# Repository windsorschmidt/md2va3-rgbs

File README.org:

* About

RGBS video and audio output board for Sega Genesis 2 VA3.

Based on the "Triple Bypass" (3BP for short) circuit originally from
René Richard.  Unlike the TBP which can be configured to work with
several types of Genesis consoles, this board is designed specifically
for the Genesis 2 VA3.

* Features

- Active buffer/amplifiers for audio and video
- Mounts inside console beside main PCB using existing mounting points
- RGBS output on DE-15 (VGA style) connector
- Audio output on 3.5mm phono jack

[[md2va3-rgbs.png?raw=true]]

* Status

Revision 2 PCB tested working.

* References

- https://github.com/db-electronics/triple-bypass-kicad
- https://github.com/tianfeng33/triple-bypass-Version-2

* License

Circuit schematic and PCB layout are licensed under CERN-OHL-S v2.

See [[LICENSE.txt]].

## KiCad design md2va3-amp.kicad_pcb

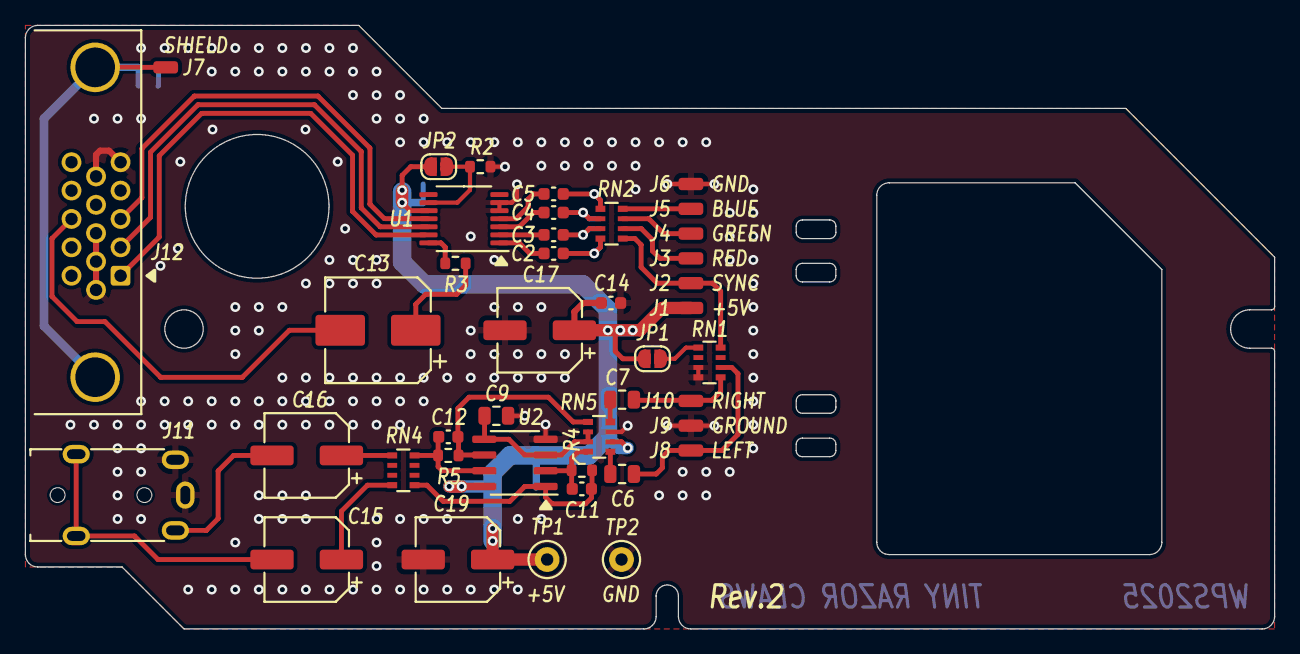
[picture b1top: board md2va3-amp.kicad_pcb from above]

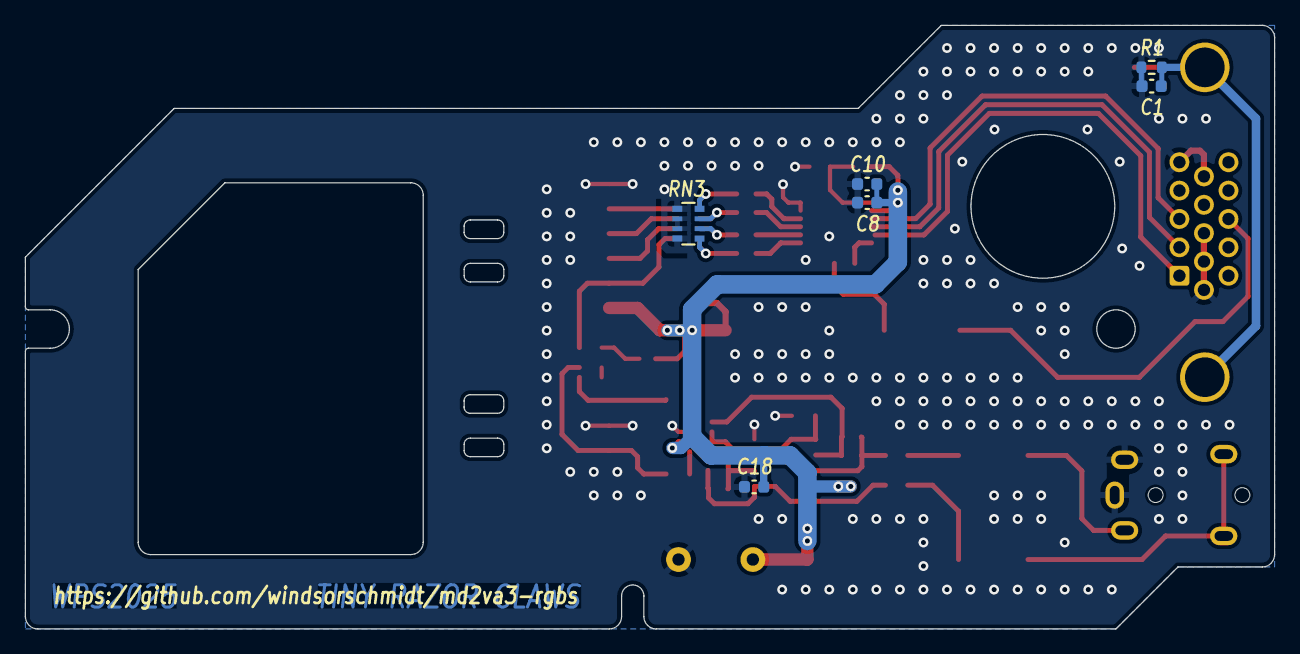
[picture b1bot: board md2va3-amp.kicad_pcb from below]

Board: 2 copper layers, 100.8 x 48.7 mm, 49 parts (6 on the bottom side), 36 nets.

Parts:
C1, C11, C12: 33p; C_0603_1608Metric
C2, C3, C4, C5, C14, C18: 100n; C_0603_1608Metric
C6, C7, C9: 10u; C_0805_2012Metric
C8: 10n; C_0603_1608Metric
C10: 1u; C_0603_1608Metric
C13: 220u; CP_Elec_8x6.2
C15, C16, C17, C19: 47u; CP_Elec_6.3x5.9
J1: +5V; SolderWirePad_1x01_SMD_1x2mm
J2: SYNC_TTL; SolderWirePad_1x01_SMD_1x2mm
J3: R; SolderWirePad_1x01_SMD_1x2mm
J4: G; SolderWirePad_1x01_SMD_1x2mm
J5: B; SolderWirePad_1x01_SMD_1x2mm
J6, J9: GND; SolderWirePad_1x01_SMD_1x2mm
J7: SHIELD; SolderWirePad_1x01_SMD_1x2mm
J8: LEFT; SolderWirePad_1x01_SMD_1x2mm
J10: RIGHT; SolderWirePad_1x01_SMD_1x2mm
J11: 54-00174; Jack_3.5mm_Tensility_54-00174
J12: HD15-SN-25; DSUB-15-HD_Female_Horizontal_P2.29x1.98mm_EdgePinOffset3.03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
JP1: SYNC_PU; SolderJumper-2_P1.3mm_Open_RoundedPad1.0x1.5mm
JP2: LPF; SolderJumper-2_P1.3mm_Open_RoundedPad1.0x1.5mm
MNT1, MNT2: MOUNT_ZIP_TIE; MountingHole_Zip_Tie
R1: 1M; R_0603_1608Metric
R2: 4.7k; R_0603_1608Metric
R3: 75; R_0603_1608Metric
R4, R5: 300k; R_0603_1608Metric
RN1: 2.2k; R_Array_Convex_4x0603
RN2: 5.62k; R_Array_Convex_4x0603
RN3: 1k; R_Array_Convex_4x0603
RN4: 330; R_Array_Convex_4x0603
RN5: 10k; R_Array_Convex_4x0603
TP1: +5V; TestPoint_Loop_D2.50mm_Drill1.0mm
TP2: GND; TestPoint_Loop_D2.50mm_Drill1.0mm
U1: THS7374; TSSOP-14_4.4x5mm_P0.65mm
U2: TLV9162IDR; SOIC-8_3.9x4.9mm_P1.27mm

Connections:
+5V: C8.1, C10.2, C14.1, C17.1, C18.1, C19.1, J1.1, JP1.1 (A), JP2.1 (A), RN5.6 (R3.2), TP1.1, U1.10 (V_{S+}), U2.8 (V+)
/B: J5.1, RN2.4 (R4.1)
/B_IN: C5.1, U1.4 (CH4_IN)
/B_OUT: J12.3, U1.11 (CH4_OUT)
/G: J4.1, RN2.3 (R3.1)
/G_IN: C4.1, U1.3 (CH3_IN)
/G_OUT: J12.2, U1.12 (CH3_OUT)
/LEFT: C6.1, J8.1, RN1.2 (R2.1)
/LEFT_OUT: C15.2, J11.T
/R: J3.1, RN2.2 (R2.1)
/RIGHT: C7.1, J10.1, RN1.1 (R1.1)
/RIGHT_OUT: C16.2, J11.R1
/R_IN: C3.1, U1.2 (CH2_IN)
/R_OUT: J12.1, U1.13 (CH2_OUT)
/SYNC_75: C13.2, J12.13
/SYNC_TTL: J2.1, RN1.4 (R4.1), RN2.1 (R1.1)
/SYNC_TTL_IN: C2.1, U1.1 (CH1_IN)
GND: C1.1, C8.2, C9.2, C10.1, C14.2, C17.2, C18.2, C19.2, J6.1, J9.1, J11.R2, J11.S, J12.5, J12.6, J12.7, J12.8, J12.10, R1.1, R2.1, RN1.7 (R2.2), RN1.8 (R1.2), RN3.5 (R4.2), RN3.6 (R3.2), RN3.7 (R2.2), RN3.8 (R1.2), RN5.7 (R2.2), TP2.1, U1.5 (GND), U1.6 (DISABLE), U2.4 (V-)
GNDPWR: C1.2, J7.1, J12.0, R1.2
unnamed: C13.1, R3.2
unnamed: JP1.2 (B), RN1.5 (R4.2)
unnamed: JP2.2 (B), R2.2, U1.9 (BYPASS)
unnamed: C2.2, RN2.8 (R1.2), RN3.1 (R1.1)
unnamed: C3.2, RN2.7 (R2.2), RN3.2 (R2.1)
unnamed: C4.2, RN2.6 (R3.2), RN3.3 (R3.1)
unnamed: C5.2, RN2.5 (R4.2), RN3.4 (R4.1)
unnamed: C11.2, R4.2, RN4.1 (R1.1), U2.1
unnamed: C15.1, RN4.8 (R1.2)
unnamed: C12.2, R5.2, RN4.4 (R4.1), U2.7
unnamed: C16.1, RN4.5 (R4.2)
unnamed: C12.1, R5.1, RN5.1 (R1.1), U2.6 (-)
unnamed: C7.2, RN5.8 (R1.2)
unnamed: C9.1, RN5.2 (R2.1), RN5.3 (R3.1), U2.3 (+), U2.5 (+)
unnamed: C11.1, R4.1, RN5.4 (R4.1), U2.2 (-)
unnamed: C6.2, RN5.5 (R4.2)
unnamed: R3.1, U1.14 (CH1_OUT)

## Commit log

2025-08-08 better 3D model for d-sub connector
2025-08-08 update pcb images
2025-08-19 update pcb image
2025-08-19 rename kicad project
2025-08-20 renme files

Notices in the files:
md2va3-amp.kicad_pcb:
Copyright Windsor Schmidt 2025.
This source describes Open Hardware and is licensed under the CERN-OHL-S v2.
under the terms of the CERN-OHL-S v2 (https://ohwr.org/cern_ohl_s_v2.txt).
